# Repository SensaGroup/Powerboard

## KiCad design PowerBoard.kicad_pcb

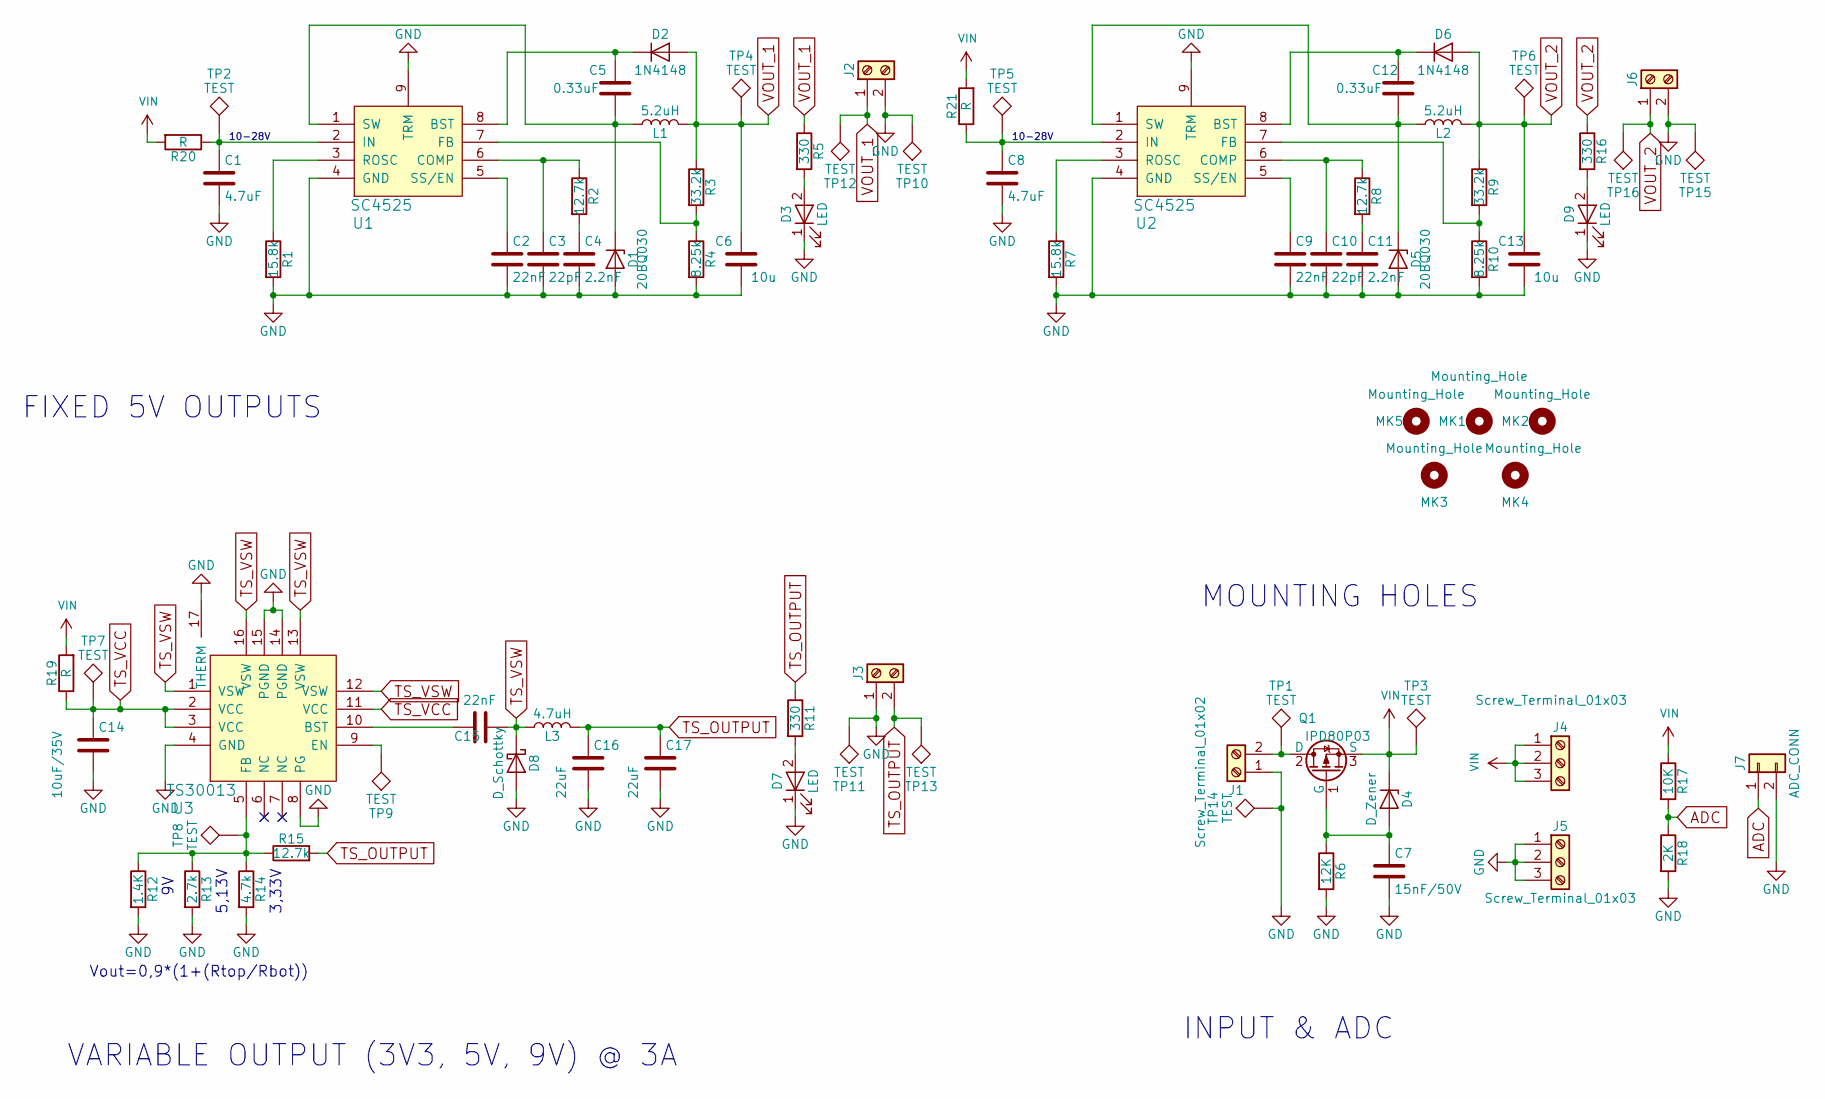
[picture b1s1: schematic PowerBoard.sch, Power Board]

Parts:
C1, C8: 4.7uF; C_1210
C2, C9: 22nF; C_0603_HandSoldering
C3, C10: 22pF; C_0603_HandSoldering
C4, C11: 2.2nF; C_0805
C5, C12: 0.33uF; C_0805
C6, C13: 10u; C_1210
C7: 15nF/50V; C_0805
C14: 10uF/35V; C_0805_HandSoldering
C15: 22nF; C_0805
C16, C17: 22uF; C_0805_HandSoldering
D1, D5: 20BQ030; D_SMB
D2, D6: 1N4148; D_SOD-523
D3, D7, D9: LED; LED_0805
D4: D_Zener; D_SOD-323_HandSoldering
D8: D_Schottky; D_MELF
J1, J2, J3, J6: Screw_Terminal_01x02; TerminalBlock_Phoenix_MKDS1.5-2pol
J4, J5: Screw_Terminal_01x03; TerminalBlock_Phoenix_MKDS1.5-3pol
J7: ADC_CONN; GS2
L1, L2: 5.2uH; L_7.3x7.3_H4.5
L3: 4.7uH; L_Taiyo-Yuden_NR-60xx
MK1, MK2, MK3, MK4, MK5: Mounting_Hole; MountingHole_2.2mm_M2
Q1: IPD80P03; TO-252-2
R1, R7: 15.8k; R_0603_HandSoldering
R2, R8, R15: 12.7k; R_0603_HandSoldering
R3, R9: 33.2k; R_0603_HandSoldering
R4, R10: 8.25k; R_0603_HandSoldering
R5, R11, R16: 330; R_0603_HandSoldering
R6: 12K; R_0603_HandSoldering
R12: 1.4K; R_0603_HandSoldering
R13: 2.7k; R_0603_HandSoldering
R14: 4.7k; R_0603_HandSoldering
R17: 10K; R_0603_HandSoldering
R18: 2K; R_0603_HandSoldering
R19, R20, R21: R; R_0805
TP1, TP2, TP3, TP4, TP5, TP6, TP7, TP8, TP9, TP10, TP11, TP12, TP13, TP14, TP15, TP16: TEST; FIDUCIAL-FRAME-1_5MM
U1, U2: SC4525; HTSOP-8-1EP_3.9x4.9mm_Pitch1.27mm_ThermalVias_LargeCopper
U3: TS30013; QFN-16-1EP_3x3mm_Pitch0.5mm_ThermalVias

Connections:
ADC: J7.1, R17.2, R18.1
GND: C1.2, C2.2, C3.2, C4.2, C6.2, C7.2, C8.2, C9.2, C10.2, C11.2, C13.2, C14.2, C16.2, C17.2, D1.2 (A), D3.1 (K), D5.2 (A), D7.1 (K), D8.2 (A), D9.1 (K), J1.1, J2.2, J3.1, J5.1, J5.2, J5.3, J6.2, J7.2, R1.2, R4.2, R6.2, R7.2, R10.2, R12.2, R13.2, R14.2, R18.2, TP10.1, TP11.1, TP14.1, TP15.1, U1.4 (GND), U1.9 (TRM), U2.4 (GND), U2.9 (TRM), U3.4 (GND), U3.8 (PG), U3.14 (PGND), U3.15 (PGND), U3.17 (THERM)
unnamed: C1.1, R20.1, TP2.1, U1.2 (IN)
unnamed: C2.1, U1.5 (SS/EN)
unnamed: C3.1, R2.1, U1.6 (COMP)
unnamed: C4.1, R2.2
unnamed: C5.1, D2.1 (K), U1.8 (BST)
unnamed: C5.2, D1.1 (K), L1.1, U1.1 (SW)
unnamed: C7.1, D4.2 (A), Q1.1 (G), R6.1
unnamed: C8.1, R21.1, TP5.1, U2.2 (IN)
unnamed: C9.1, U2.5 (SS/EN)
unnamed: C10.1, R8.1, U2.6 (COMP)
unnamed: C11.1, R8.2
unnamed: C12.1, D6.1 (K), U2.8 (BST)
unnamed: C12.2, D5.1 (K), L2.1, U2.1 (SW)
unnamed: C15.2, U3.10 (BST)
unnamed: D3.2 (A), R5.2
unnamed: D7.2 (A), R11.2
unnamed: D9.2 (A), R16.2
unnamed: J1.2, Q1.2 (D), TP1.1
unnamed: R1.1, U1.3 (ROSC)
unnamed: R3.2, R4.1, U1.7 (FB)
unnamed: R7.1, U2.3 (ROSC)
unnamed: R9.2, R10.1, U2.7 (FB)
unnamed: R12.1, R13.1, R14.1, R15.1, TP8.1, U3.5 (FB)
unnamed: TP9.1, U3.9 (EN)
TS_OUTPUT: C16.1, C17.1, J3.2, L3.2, R11.1, R15.2, TP13.1
TS_VCC: C14.1, R19.1, TP7.1, U3.2 (VCC), U3.3 (VCC), U3.11 (VCC)
TS_VSW: C15.1, D8.1 (K), L3.1, U3.1 (VSW), U3.12 (VSW), U3.13 (VSW), U3.16 (VSW)
VIN: D4.1 (K), J4.1, J4.2, J4.3, Q1.3 (S), R17.1, R19.2, R20.2, R21.2, TP3.1
VOUT_1: C6.1, D2.2 (A), J2.1, L1.2, R3.1, R5.1, TP4.1, TP12.1
VOUT_2: C13.1, D6.2 (A), J6.1, L2.2, R9.1, R16.1, TP6.1, TP16.1

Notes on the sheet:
10-28V
FIXED 5V OUTPUTS
3,33V
5,13V
Vout=0,9*(1+(Rtop/Rbot))
VARIABLE OUTPUT (3V3, 5V, 9V) @ 3A
INPUT & ADC
MOUNTING HOLES

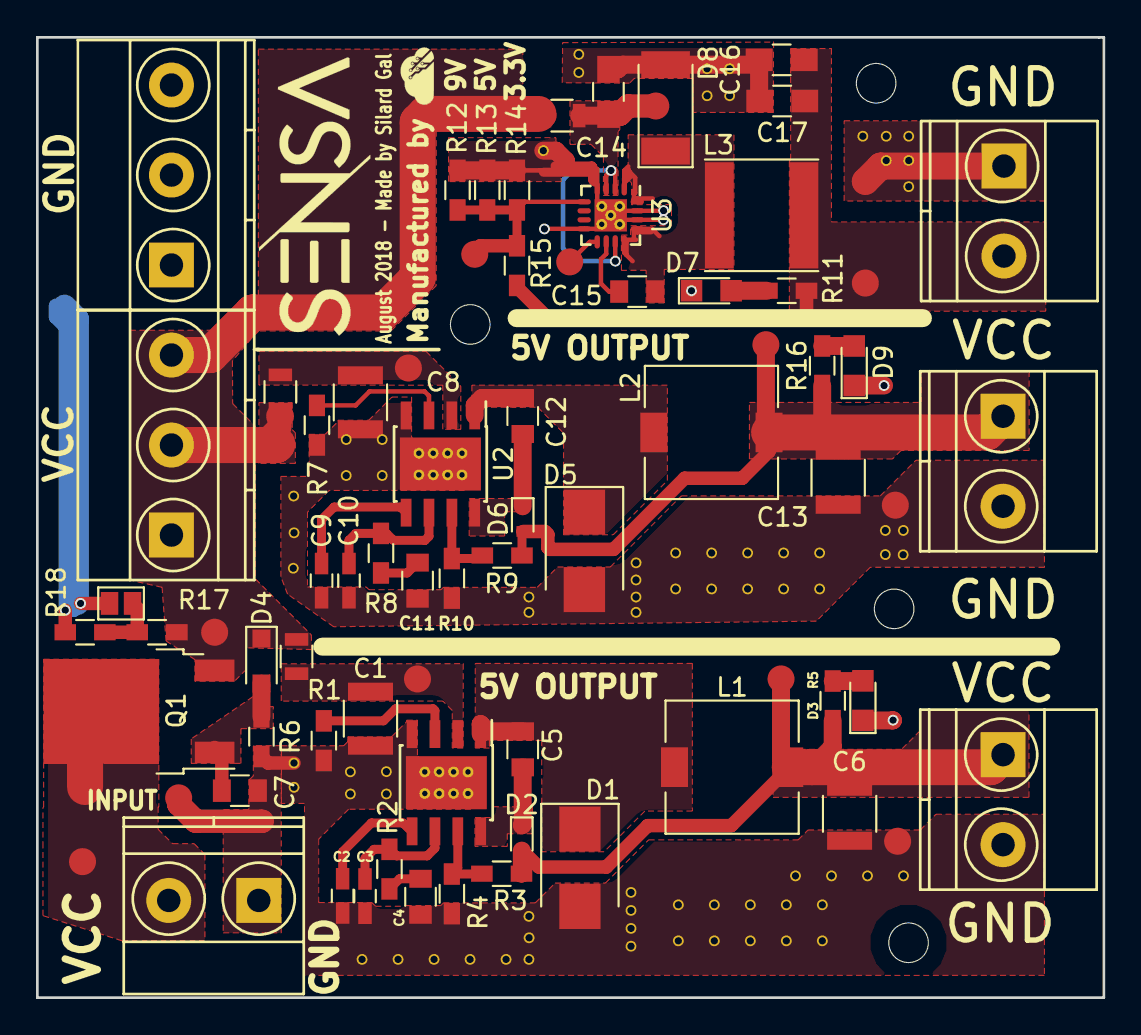
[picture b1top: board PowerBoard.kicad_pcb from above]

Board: 2 copper layers, 59.2 x 53.3 mm, 81 parts (0 on the bottom side), 32 nets.

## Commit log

2018-08-30 Push all files
2018-08-30 README
